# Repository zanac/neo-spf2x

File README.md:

# Neo Geo AES/MVS cartridge with microSD: format, packer, loader and gateware

🇬🇧 English · [🇮🇹 Italiano](README.it.md)

A Neo Geo cartridge (AES and MVS) that loads a game from a microSD card. The software side
(format, packer, loader) is written and tested; the FPGA gateware is simulated but not proven
on a console; the PCBs are not designed yet (the partition is in `docs/PCB.md`). See
`docs/ARCHITECTURE.md` for the status and the open points.

**Documentation is kept in English (`docs/`, this README) and in Italian (`docs/it/`,
`README.it.md`), and both versions are updated together** (`tests/check_docs.py`).

## Contents

| Path | What |
|------|------|
| `docs/FORMAT.md` | Specification of the `.ngpk` format and of the recipes |
| `docs/MVS.md`, `docs/PCB.md` | MVS/AES differences, MVS pinout and board partition (AES + MVS) |
| `docs/AES_PINOUT.md` | Signal names and pin numbers of the AES PROG and CHA connectors |
| `docs/TIMING.md` | Sprite, fix, bank switching and NEO-ZMC behaviour derived from Geolith, with what is missing |
| `docs/ARCHITECTURE.md` | Architecture, SDRAM map, contract with the FPGA, open points |
| `tools/ngpk.py` | Packer/inspector (Python 3, no dependencies) |
| `recipes/` | Recipes: Samurai Shodown III (example) and `spf2ng` (the project's game) |
| `docs/GATEWARE.md` | Status of the Verilog gateware and what the tests prove |
| `gateware/` | RTL and testbenches (Icarus Verilog): sprite (AES and MVS), fix, P bank, Z80 bank, SDRAM controller, arbiter, top |
| `docs/BOOT.md` | How the console sees the cartridge during loading (boot stub) |
| `boot/` | 68k source of the stub (`stub.S`) and binary |
| `docs/PROTECTIONS.md` | Protected games and special cartridges (from MAME): what each needs, 128 MiB, open risks |
| `docs/COMPONENTS.md` | I/O budget, choice of FPGA, SDRAM, MCU, translators and open hardware points |
| `hardware/` | `gen_signals.py`, `signals.csv` (162 AES signals), `signals_mvs.csv` (184 MVS pins), `mvs_pins.csv`, `extract_kicad_pins.py` |
| `firmware/` | `.ngpk` parser and loader in portable C99, plus PC tests |
| `tests/` | Packer tests, documentation check and the script that runs everything |

ROM files are not included: you need your own dumps.

**License:** GPL-3.0-or-later, text in `LICENSE`.

## Usage

```sh
# create a package (the recipe lists the files, --base-dir says where they are)
python3 tools/ngpk.py pack recipes/samsho3.json --base-dir /path/to/romset -o samsho3.ngpk

python3 tools/ngpk.py info   samsho3.ngpk    # regions, sizes, CRC
python3 tools/ngpk.py verify samsho3.ngpk    # re-check the CRCs
python3 tools/ngpk.py unpack samsho3.ngpk -o out/   # P.bin, C.bin, ...
# unpack --canonical brings C and S back to MAME order; pack uses the sdram1 layout (docs/FORMAT.md)

# tests (without ROMs it uses a synthetic game; with a folder it also uses the romset)
tests/run_all.sh
tests/run_all.sh /path/to/romset
```

Copy the `.ngpk` files onto the microSD: the loader reads them through the MCU's file system
(FatFS).

## Adding a game

Write a recipe (see `docs/FORMAT.md`): which files go in which region and with which
operation (`concat`, `swap16`, `interleave8`). The packer checks that `NEO-GEO` is at `0x100`
of the P, so a wrong swap does not go unnoticed. Games requiring protections or encryption
(SMA, PCM2, CMC, PVC...) are not supported yet and are rejected.

## Porting the loader to an MCU

`firmware/ngsd_loader.c` does not depend on the hardware. Four functions in `ngsd_hal_t` are
implemented: reading from the file on the SD (FatFS), writing into SDRAM through the FPGA,
writing the FPGA registers and, if needed, a progress bar. The code compiles with `-std=c99`
without libraries.

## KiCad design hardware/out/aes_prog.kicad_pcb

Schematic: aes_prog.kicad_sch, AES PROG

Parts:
C1, C2, C3, C4, C5, C6, C7, C8, C9, C10, C11, C12, C13, C14, C15, C16, C17, C18, C19, C20, C21, C22, C23, C24, C27, C28, C29, C30, C31, C32, C33, C34, C35, C36, C38, C42: 100n; C_0402_1005Metric
C25, C26: 22u; C_1206_3216Metric
C37, C39: 1u; C_0402_1005Metric
C40, C41: 15p; C_0402_1005Metric
D1: MCU; LED_0603_1608Metric
J1: AES PROG edge A; neogeo-aes-a-side-edge
J2: AES PROG edge B; neogeo-aes-b-side-edge
J3: LINK1; Hirose_DF12NB3.0-80DP-0.5V51_2x40_P0.50mm_Vertical
J4: LINK2; Hirose_DF12NB3.0-80DP-0.5V51_2x40_P0.50mm_Vertical
J5: microSD; microSD_HC_Hirose_DM3AT-SF-PEJM5
J6: USB/SWD pads; PinHeader_1x04_P1.27mm_Vertical
J7: SWD; PinHeader_1x03_P1.27mm_Vertical
R1, R2, R3, R4, R5, R6: 10k; R_0402_1005Metric
R7, R10, R11: 1k; R_0402_1005Metric
R8, R9: 27; R_0402_1005Metric
R12: 0; R_0402_1005Metric
SW1: RESET; SW_SPST_PTS810
SW2: BOOTSEL; SW_SPST_PTS810
U1, U2, U3, U4, U5, U6: SN74ALVC164245DGG; TSSOP-48_6.1x12.5mm_P0.5mm
U7: RP2040; QFN-56-1EP_7x7mm_P0.4mm_EP3.2x3.2mm
U8: W25Q128JVS; SOIC-8W_5.3x5.3mm_P1.27mm
Y1: 12MHz ABM8-272-T3; Crystal_SMD_3225-4Pin_3.2x2.5mm

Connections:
4MB: J4.29, U4.29 (2A6)
68KCLKB: J3.65, U3.30 (2A5)
+3V3: C1.1, C2.1, C5.1, C6.1, C9.1, C10.1, C13.1, C14.1, C17.1, C18.1, C21.1, C22.1, C26.1, C27.1, C28.1, C29.1, C30.1, C31.1, C32.1, C33.1, C34.1, C35.1, C36.1, C39.1, C42.1, J4.46, J4.47, J4.48, J5.4 (VDD), R1.2, R2.2, R3.2, R4.2, R5.2, R6.2, U1.31 (VCCA), U1.42 (VCCA), U2.31 (VCCA), U2.42 (VCCA), U3.31 (VCCA), U3.42 (VCCA), U4.31 (VCCA), U4.42 (VCCA), U5.1 (1DIR), U5.31 (VCCA), U5.42 (VCCA), U6.25 (2~OE), U6.31 (VCCA), U6.42 (VCCA), U7.1 (IOVDD), U7.10 (IOVDD), U7.22 (IOVDD), U7.33 (IOVDD), U7.42 (IOVDD), U7.43 (ADC_AVDD), U7.44 (VREG_IN), U7.48 (USB_VDD), U7.49 (IOVDD), U8.8 (VCC)
+5V: C3.1, C4.1, C7.1, C8.1, C11.1, C12.1, C15.1, C16.1, C19.1, C20.1, C23.1, C24.1, C25.1, J1.25, J1.26, J1.27, J2.25, J2.26, J2.27, J4.49, J4.50, J6.4, U1.7 (VCCB), U1.18 (VCCB), U2.7 (VCCB), U2.18 (VCCB), U3.7 (VCCB), U3.18 (VCCB), U4.7 (VCCB), U4.18 (VCCB), U5.7 (VCCB), U5.18 (VCCB), U6.7 (VCCB), U6.18 (VCCB)
A1: J3.2, U2.47 (1A1)
A2: J3.5, U2.46 (1A2)
A3: J3.7, U2.44 (1A3)
A4: J3.10, U2.43 (1A4)
A5: J3.13, U2.41 (1A5)
A6: J3.15, U2.40 (1A6)
A7: J3.18, U2.38 (1A7)
A8: J3.21, U2.37 (1A8)
A9: J3.23, U2.36 (2A1)
A10: J3.26, U2.35 (2A2)
A11: J3.29, U2.33 (2A3)
A12: J3.31, U2.32 (2A4)
A13: J3.34, U2.30 (2A5)
A14: J3.37, U2.29 (2A6)
A15: J3.39, U2.27 (2A7)
A16: J3.42, U2.26 (2A8)
A17: J3.45, U3.46 (1A2)
A18: J3.47, U3.43 (1A4)
A19: J3.50, U3.40 (1A6)
AS: J3.46, U3.44 (1A3)
BOOTSEL_N: R7.1, SW2.1
D0: J3.1, U1.47 (1A1)
D1: J3.3, U1.46 (1A2)
D2: J3.6, U1.44 (1A3)
D3: J3.9, U1.43 (1A4)
D4: J3.11, U1.41 (1A5)
D5: J3.14, U1.40 (1A6)
D6: J3.17, U1.38 (1A7)
D7: J3.19, U1.37 (1A8)
D8: J3.22, U1.36 (2A1)
D9: J3.25, U1.35 (2A2)
D10: J3.27, U1.33 (2A3)
D11: J3.30, U1.32 (2A4)
D12: J3.33, U1.30 (2A5)
D13: J3.35, U1.29 (2A6)
D14: J3.38, U1.27 (2A7)
D15: J3.41, U1.26 (2A8)
DIR_D: J4.42, U1.1 (1DIR), U1.24 (2DIR)
DIR_SDPAD: J4.43, U6.1 (1DIR)
DIR_SDRAD: J4.45, U5.24 (2DIR)
GND: C1.2, C2.2, C3.2, C4.2, C5.2, C6.2, C7.2, C8.2, C9.2, C10.2, C11.2, C12.2, C13.2, C14.2, C15.2, C16.2, C17.2, C18.2, C19.2, C20.2, C21.2, C22.2, C23.2, C24.2, C25.2, C26.2, C27.2, C28.2, C29.2, C30.2, C31.2, C32.2, C33.2, C34.2, C35.2, C36.2, C37.2, C38.2, C39.2, C40.2, C41.2, C42.2, J1.1, J1.2, J1.49, J1.50, J2.1, J2.2, J2.49, J2.50, J3.4, J3.8, J3.12, J3.16, J3.20, J3.24, J3.28, J3.32, J3.36, J3.40, J3.44, J3.48, J3.52, J3.56, J3.60, J3.64, J3.68, J3.72, J3.76, J3.80, J4.4, J4.8, J4.12, J4.16, J4.20, J4.24, J4.28, J4.32, J4.36, J4.40, J4.44, J4.51, J4.52, J4.53, J4.54, J4.55, J4.56, J4.57, J4.58, J4.59, J4.60, J4.61, J4.62, J4.63, J4.64, J4.65, J4.66, J4.67, J4.68, J4.69, J4.70, J4.71, J4.72, J4.73, J4.74, J4.75, J4.76, J4.77, J4.78, J4.79, J4.80, J5.6 (VSS), J5.10 (DET_A), J5.11 (SHIELD), J6.3, J7.2, R12.2, SW1.2, SW2.2, U1.4 (GND), U1.10 (GND), U1.15 (GND), U1.21 (GND), U1.28 (GND), U1.34 (GND), U1.39 (GND), U1.45 (GND), U2.1 (1DIR), U2.4 (GND), U2.10 (GND), U2.15 (GND), U2.21 (GND), U2.24 (2DIR), U2.28 (GND), U2.34 (GND), U2.39 (GND), U2.45 (GND), U3.1 (1DIR), U3.4 (GND), U3.10 (GND), U3.15 (GND), U3.21 (GND), U3.24 (2DIR), U3.28 (GND), U3.34 (GND), U3.39 (GND), U3.45 (GND), U4.1 (1DIR), U4.4 (GND), U4.10 (GND), U4.15 (GND), U4.21 (GND), U4.22 (2B7), U4.23 (2B8), U4.24 (2DIR), U4.26 (2A8), U4.27 (2A7), U4.28 (GND), U4.34 (GND), U4.39 (GND), U4.45 (GND), U5.4 (GND), U5.8 (1B5), U5.9 (1B6), U5.10 (GND), U5.11 (1B7), U5.12 (1B8), U5.15 (GND), U5.21 (GND), U5.28 (GND), U5.34 (GND), U5.37 (1A8), U5.38 (1A7), U5.39 (GND), U5.40 (1A6), U5.41 (1A5), U5.45 (GND), U6.4 (GND), U6.10 (GND), U6.13 (2B1), U6.14 (2B2), U6.15 (GND), U6.16 (2B3), U6.17 (2B4), U6.19 (2B5), U6.20 (2B6), U6.21 (GND), U6.22 (2B7), U6.23 (2B8), U6.24 (2DIR), U6.26 (2A8), U6.27 (2A7), U6.28 (GND), U6.29 (2A6), U6.30 (2A5), U6.32 (2A4), U6.33 (2A3), U6.34 (GND), U6.35 (2A2), U6.36 (2A1), U6.39 (GND), U6.45 (GND), U7.19 (TESTEN), U7.57 (GND), U8.4 (GND), Y1.2, Y1.4
LED_A: D1.2 (A), R11.1
LED_K: D1.1 (K), R12.1
LED_MCU: R11.2, U7.37 (GPIO25)
MCU_INT: J4.41, U7.17 (GPIO14)
MCU_RUN: J4.39, U7.16 (GPIO13)
OE_PRG_N: J4.38, U1.25 (2~OE), U1.48 (1~OE), U2.25 (2~OE), U2.48 (1~OE), U3.25 (2~OE), U3.48 (1~OE), U4.25 (2~OE), U4.48 (1~OE), U5.25 (2~OE), U5.48 (1~OE), U6.48 (1~OE)
PDTACK: J3.63, U5.43 (1A4)
PORTADRS: J4.27, U4.30 (2A5)
PORTOEL: J3.57, U3.35 (2A2)
PORTOEU: J3.54, U3.36 (2A1)
PORTWEL: J3.62, U3.32 (2A4)
PORTWEU: J3.59, U3.33 (2A3)
PWAIT0: J3.61, U5.44 (1A3)
PWAIT1: J3.58, U5.46 (1A2)
QSPI_SCLK: U7.52 (QSPI_SCLK), U8.6 (CLK)
QSPI_SD0: U7.53 (QSPI_SD0), U8.5 (DI(IO0))
QSPI_SD1: U7.55 (QSPI_SD1), U8.2 (DO(IO1))
QSPI_SD2: U7.54 (QSPI_SD2), U8.3 (IO2)
QSPI_SD3: U7.51 (QSPI_SD3), U8.7 (IO3)
QSPI_SS: R7.2, U7.56 (QSPI_SS), U8.1 (~CS)
RESET: J3.67, U3.29 (2A6)
ROMOE: J3.53, U3.37 (1A8)
ROMOEL: J3.51, U3.38 (1A7)
ROMOEU: J3.49, U3.41 (1A5)
ROMWAIT: J3.55, U5.47 (1A1)
RP_DVDD: C37.1, C38.1, U7.23 (DVDD), U7.45 (VREG_VOUT), U7.50 (DVDD)
RP_RUN: R6.1, SW1.1, U7.26 (RUN)
R_W: J3.43, U3.47 (1A1)
SDPA8: J4.11, U4.47 (1A1)
SDPA9: J4.14, U4.44 (1A3)
SDPA10: J4.17, U4.41 (1A5)
SDPA11: J4.19, U4.38 (1A7)
SDPAD0: J3.70, U6.47 (1A1)
SDPAD1: J3.73, U6.46 (1A2)
SDPAD2: J3.75, U6.44 (1A3)
SDPAD3: J3.78, U6.43 (1A4)
SDPAD4: J4.1, U6.41 (1A5)
SDPAD5: J4.3, U6.40 (1A6)
SDPAD6: J4.6, U6.38 (1A7)
SDPAD7: J4.9, U6.37 (1A8)
SDPMPX: J4.22, U4.36 (2A1)
SDPOE: J4.25, U4.33 (2A3)
SDRA8: J4.7, U3.27 (2A7)
SDRA9: J4.10, U3.26 (2A8)
SDRA20: J4.13, U4.46 (1A2)
SDRA21: J4.15, U4.43 (1A4)
SDRA22: J4.18, U4.40 (1A6)
SDRA23: J4.21, U4.37 (1A8)
SDRAD0: J3.66, U5.36 (2A1)
SDRAD1: J3.69, U5.35 (2A2)
SDRAD2: J3.71, U5.33 (2A3)
SDRAD3: J3.74, U5.32 (2A4)
SDRAD4: J3.77, U5.30 (2A5)
SDRAD5: J3.79, U5.29 (2A6)
SDRAD6: J4.2, U5.27 (2A7)
SDRAD7: J4.5, U5.26 (2A8)
SDRMPX: J4.23, U4.35 (2A2)
SDROE: J4.26, U4.32 (2A4)
SD_CLK: J5.5 (CLK), U7.8 (GPIO6)
SD_CMD: J5.3 (CMD), R5.1, U7.9 (GPIO7)
SD_D0: J5.7 (DAT0), R1.1, U7.11 (GPIO8)
SD_D1: J5.8 (DAT1), R2.1, U7.12 (GPIO9)
SD_D2: J5.1 (DAT2), R3.1, U7.13 (GPIO10)
SD_D3: J5.2 (DAT3/CD), R4.1, U7.14 (GPIO11)
SD_DET: J5.9 (DET_B), U7.15 (GPIO12)
SPI_CS_N: J4.31, U7.3 (GPIO1)
SPI_IO0: J4.33, U7.4 (GPIO2)
SPI_IO1: J4.34, U7.5 (GPIO3)
SPI_IO2: J4.35, U7.6 (GPIO4)
SPI_IO3: J4.37, U7.7 (GPIO5)
SPI_SCLK: J4.30, U7.2 (GPIO0)
SWCLK: J7.1, U7.24 (SWCLK)
SWD: J7.3, U7.25 (SWD)
USB_DM: J6.1, R8.2
USB_DM_R: R8.1, U7.46 (USB_DM)
USB_DP: J6.2, R9.2
USB_DP_R: R9.1, U7.47 (USB_DP)
XIN: C40.1, U7.20 (XIN), Y1.1
XOUT: R10.1, U7.21 (XOUT)
XOUT_R: C41.1, R10.2, Y1.3
X_4MB: J2.48, U4.20 (2B6)
X_68KCLKB: J1.32, U3.19 (2B5)
X_A1: J2.3, U2.2 (1B1)
X_A2: J2.4, U2.3 (1B2)
X_A3: J2.5, U2.5 (1B3)
X_A4: J2.6, U2.6 (1B4)
X_A5: J2.7, U2.8 (1B5)
X_A6: J2.8, U2.9 (1B6)
X_A7: J2.9, U2.11 (1B7)
X_A8: J2.10, U2.12 (1B8)
X_A9: J2.11, U2.13 (2B1)
X_A10: J2.12, U2.14 (2B2)
X_A11: J2.13, U2.16 (2B3)
X_A12: J2.14, U2.17 (2B4)
X_A13: J2.15, U2.19 (2B5)
X_A14: J2.16, U2.20 (2B6)
X_A15: J2.17, U2.22 (2B7)
X_A16: J2.18, U2.23 (2B8)
X_A17: J2.19, U3.3 (1B2)
X_A18: J2.20, U3.6 (1B4)
X_A19: J2.21, U3.9 (1B6)
X_AS: J1.20, U3.5 (1B3)
X_D0: J1.3, U1.2 (1B1)
X_D1: J1.4, U1.3 (1B2)
X_D2: J1.5, U1.5 (1B3)
X_D3: J1.6, U1.6 (1B4)
X_D4: J1.7, U1.8 (1B5)
X_D5: J1.8, U1.9 (1B6)
X_D6: J1.9, U1.11 (1B7)
X_D7: J1.10, U1.12 (1B8)
X_D8: J1.11, U1.13 (2B1)
X_D9: J1.12, U1.14 (2B2)
X_D10: J1.13, U1.16 (2B3)
X_D11: J1.14, U1.17 (2B4)
X_D12: J1.15, U1.19 (2B5)
X_D13: J1.16, U1.20 (2B6)
X_D14: J1.17, U1.22 (2B7)
X_D15: J1.18, U1.23 (2B8)
X_PDTACK: J2.31, U5.6 (1B4)
X_PORTADRS: J1.48, U4.19 (2B5)
X_PORTOEL: J1.29, U3.14 (2B2)
X_PORTOEU: J1.28, U3.13 (2B1)
X_PORTWEL: J1.31, U3.17 (2B4)
X_PORTWEU: J1.30, U3.16 (2B3)
X_PWAIT0: J2.30, U5.5 (1B3)
X_PWAIT1: J2.29, U5.3 (1B2)
X_RESET: J1.33, U3.20 (2B6)
X_ROMOE: J2.22, U3.12 (1B8)
X_ROMOEL: J1.22, U3.11 (1B7)
X_ROMOEU: J1.21, U3.8 (1B5)
X_ROMWAIT: J2.28, U5.2 (1B1)
X_R_W: J1.19, U3.2 (1B1)
X_SDPA8: J1.42, U4.2 (1B1)
X_SDPA9: J1.43, U4.5 (1B3)
X_SDPA10: J1.44, U4.8 (1B5)
X_SDPA11: J1.45, U4.11 (1B7)
X_SDPAD0: J1.34, U6.2 (1B1)
X_SDPAD1: J1.35, U6.3 (1B2)
X_SDPAD2: J1.36, U6.5 (1B3)
X_SDPAD3: J1.37, U6.6 (1B4)
X_SDPAD4: J1.38, U6.8 (1B5)
X_SDPAD5: J1.39, U6.9 (1B6)
X_SDPAD6: J1.40, U6.11 (1B7)
X_SDPAD7: J1.41, U6.12 (1B8)
X_SDPMPX: J1.46, U4.13 (2B1)
X_SDPOE: J1.47, U4.16 (2B3)
X_SDRA8: J2.40, U3.22 (2B7)
X_SDRA9: J2.41, U3.23 (2B8)
X_SDRA20: J2.42, U4.3 (1B2)
X_SDRA21: J2.43, U4.6 (1B4)
X_SDRA22: J2.44, U4.9 (1B6)
X_SDRA23: J2.45, U4.12 (1B8)
X_SDRAD0: J2.32, U5.13 (2B1)
X_SDRAD1: J2.33, U5.14 (2B2)
X_SDRAD2: J2.34, U5.16 (2B3)
X_SDRAD3: J2.35, U5.17 (2B4)
X_SDRAD4: J2.36, U5.19 (2B5)
X_SDRAD5: J2.37, U5.20 (2B6)
X_SDRAD6: J2.38, U5.22 (2B7)
X_SDRAD7: J2.39, U5.23 (2B8)
X_SDRMPX: J2.46, U4.14 (2B2)
X_SDROE: J2.47, U4.17 (2B4)

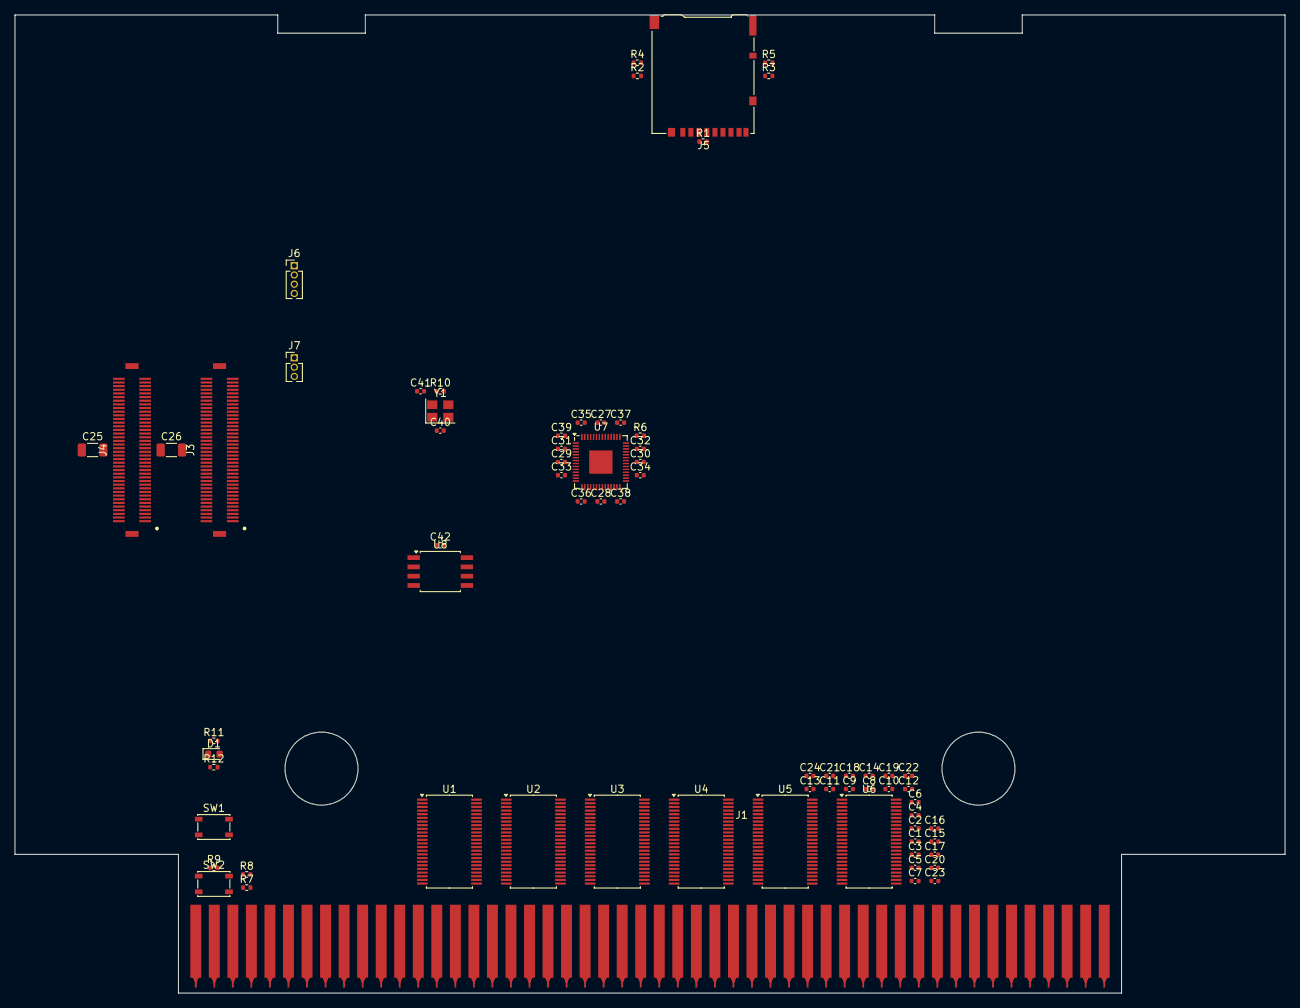
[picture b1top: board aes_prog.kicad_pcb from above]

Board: 6 copper layers, 174.0 x 134.0 mm, 73 parts (1 on the bottom side), 207 nets, no tracks yet.

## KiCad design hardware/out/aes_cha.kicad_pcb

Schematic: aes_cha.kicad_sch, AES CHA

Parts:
C1, C2, C3, C4, C5, C6, C7, C8, C9, C10, C11, C12, C13, C14, C15, C16, C17, C18, C19, C20, C21, C22, C23, C24, C28, C29, C30, C31, C32, C33, C34, C35, C36, C38, C39, C40, C41, C42, C43, C44, C45, C46, C47, C48, C49, C50, C51, C52, C53, C54, C55, C56, C57, C58, C59, C67, C68, C69, C70, C71, C72, C73, C74, C75, C77, C78, C79, C80, C81, C82, C83, C84, C94, C95, C96, C97, C98, C99, C100, C101, C102, C103, C104, C105, C106, C107, C108, C109, C110, C111, C112, C113, C114, C115, C116, C117: 100n; C_0402_1005Metric
C25, C26, C27, C37, C60, C61, C62, C63, C64, C65, C66: 10u; C_0603_1608Metric
C76, C85, C86, C93: 10u; C_0805_2012Metric
C87, C88, C89, C90, C91, C92: 22u; C_1206_3216Metric
D1: DONE; LED_0603_1608Metric
FB1: 120R@100MHz; L_0603_1608Metric
J1: JTAG; PinHeader_2x05_P1.27mm_Vertical_SMD
J2: AES CHA edge A; neogeo-aes-a-side-edge
J3: AES CHA edge B; neogeo-aes-b-side-edge
J4: LINK1; Hirose_DF12NB3.0-80DS-0.5V51_2x40_P0.50mm_Vertical
J5: LINK2; Hirose_DF12NB3.0-80DS-0.5V51_2x40_P0.50mm_Vertical
L1, L2, L3: 2.2uH NRS4018T2R2MDGJV; L_Taiyo-Yuden_NR-40xx
R1, R2, R3, R6, R7, R8, R9, R10, R11, R12, R19: 4.7k; R_0402_1005Metric
R4, R5, R25: 0; R_0402_1005Metric
R13, R24: 1k; R_0402_1005Metric
R14: 33; R_0402_1005Metric
R15, R16, R17, R18, R20, R21, R22, R23, R26, R27, R28, R29, R30, R31, R32, R33, R36: 10k; R_0402_1005Metric
R34: 453k; R_0402_1005Metric
R35, R39: 100k; R_0402_1005Metric
R37: 12k; R_0402_1005Metric
R38: 316k; R_0402_1005Metric
SW1: PROGRAMN; SW_SPST_PTS810
U1: LFE5U-45F-8BG554; BGA-554_26x26_23.0x23.0mm_P0.8mm
U2: W25Q128JVS; SOIC-8W_5.3x5.3mm_P1.27mm
U3, U4: AS4C32M16SB / IS42S16320D (512Mbit x16); TSOP-II-54_22.2x10.16mm_P0.8mm
U5, U6, U7: TLV62569; SOT-23-5
U8, U9, U10, U11, U12, U13: SN74ALVC164245DGG; TSSOP-48_6.1x12.5mm_P0.5mm

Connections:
2H1: U1.D5 (PT9A), U8.43 (1A4)
4MB: J5.29, U1.P5 (PL47B)
8M: U1.E11 (PT36A/PCLKT0_1), U11.40 (1A6)
12M: U1.D11 (PT36B/PCLKC0_1), U8.44 (1A3)
24M: U1.A2 (PT4A/ULC_GPLL1T_IN), U11.41 (1A5)
68KCLKB: J4.65, U1.B11 (PT33B/GR_PCLK0_0)
+1V1: C1.1, C2.1, C3.1, C4.1, C5.1, C6.1, C7.1, C8.1, C9.1, C10.1, C11.1, C12.1, C13.1, C14.1, C15.1, C16.1, C17.1, C18.1, C19.1, C20.1, C21.1, C22.1, C23.1, C24.1, C25.1, C26.1, C27.1, C89.1, C90.1, L2.2, R36.1, U1.K11 (VCC), U1.K12 (VCC), U1.K13 (VCC), U1.K14 (VCC), U1.K15 (VCC), U1.K16 (VCC), U1.L10 (VCC), U1.L17 (VCC), U1.M10 (VCC), U1.M17 (VCC), U1.N10 (VCC), U1.N17 (VCC), U1.P10 (VCC), U1.P17 (VCC), U1.R10 (VCC), U1.R17 (VCC), U1.T10 (VCC), U1.T11 (VCC), U1.T12 (VCC), U1.T13 (VCC), U1.T14 (VCC), U1.T15 (VCC), U1.T16 (VCC), U1.T17 (VCC)
+2V5: C91.1, C92.1, FB1.1, L3.2, R38.1
+3V3: C38.1, C39.1, C40.1, C41.1, C42.1, C43.1, C44.1, C45.1, C46.1, C47.1, C48.1, C49.1, C50.1, C51.1, C52.1, C53.1, C54.1, C55.1, C56.1, C57.1, C58.1, C59.1, C60.1, C61.1, C62.1, C63.1, C64.1, C65.1, C66.1, C67.1, C68.1, C69.1, C70.1, C71.1, C72.1, C73.1, C74.1, C75.1, C76.1, C77.1, C78.1, C79.1, C80.1, C81.1, C82.1, C83.1, C84.1, C85.1, C87.1, C88.1, C93.1, C94.1, C95.1, C98.1, C99.1, C102.1, C103.1, C106.1, C107.1, C110.1, C111.1, C114.1, C115.1, J1.1, J5.46, J5.47, J5.48, L1.2, R1.2, R2.2, R3.2, R6.2, R7.2, R8.2, R9.2, R10.2, R11.2, R13.2, R15.2, R16.2, R17.2, R18.2, R19.2, R20.2, R21.2, R23.2, R27.2, R28.2, R30.2, R31.2, R32.2, R33.2, R34.1, U1.H10 (VCCIO0), U1.H12 (VCCIO0), U1.H13 (VCCIO0), U1.H15 (VCCIO1), U1.H16 (VCCIO1), U1.H18 (VCCIO1), U1.J19 (VCCIO2), U1.K8 (VCCIO7), U1.L19 (VCCIO2), U1.M8 (VCCIO7), U1.M19 (VCCIO2), U1.N8 (VCCIO7), U1.N19 (VCCIO2), U1.P8 (VCCIO6), U1.P19 (VCCIO3), U1.R8 (VCCIO6), U1.R19 (VCCIO3), U1.U8 (VCCIO6), U1.U19 (VCCIO3), U1.V8 (VCCIO6), U1.V10 (VCCIO8), U1.V11 (VCCIO8), U2.8 (VCC), U3.1 (VDD), U3.3 (VDDQ), U3.9 (VDDQ), U3.14 (VDD), U3.27 (VDD), U3.43 (VDDQ), U3.49 (VDDQ), U4.1 (VDD), U4.3 (VDDQ), U4.9 (VDDQ), U4.14 (VDD), U4.27 (VDD), U4.43 (VDDQ), U4.49 (VDDQ), U6.1 (EN), U6.4 (VIN), U7.1 (EN), U7.4 (VIN), U8.31 (VCCA), U8.42 (VCCA), U9.31 (VCCA), U9.42 (VCCA), U10.31 (VCCA), U10.42 (VCCA), U11.24 (2DIR), U11.31 (VCCA), U11.42 (VCCA), U12.1 (1DIR), U12.24 (2DIR), U12.31 (VCCA), U12.42 (VCCA), U13.25 (2~OE), U13.31 (VCCA), U13.42 (VCCA)
+5V: C86.1, C96.1, C97.1, C100.1, C101.1, C104.1, C105.1, C108.1, C109.1, C112.1, C113.1, C116.1, C117.1, J2.25, J2.26, J2.27, J3.25, J3.26, J3.27, J5.49, J5.50, U5.1 (EN), U5.4 (VIN), U8.7 (VCCB), U8.18 (VCCB), U9.7 (VCCB), U9.18 (VCCB), U10.7 (VCCB), U10.18 (VCCB), U11.7 (VCCB), U11.18 (VCCB), U12.7 (VCCB), U12.18 (VCCB), U13.7 (VCCB), U13.18 (VCCB)
A1: J4.2, U1.E24 (PR17C)
A2: J4.5, U1.F22 (PR23A)
A3: J4.7, U1.F26 (PR20B)
A4: J4.10, U1.H26 (PR35D/PCLKC3_0)
A5: J4.13, U1.H24 (PR35A/PCLKT3_1)
A6: J4.15, U1.H21 (PR23D)
A7: J4.18, U1.J26 (PR38B)
A8: J4.21, U1.J23 (PR29B)
A9: J4.23, U1.K26 (PR41C)
A10: J4.26, U1.K25 (PR38A/GR_PCLK3_0)
A11: J4.29, U1.K22 (PR29A/GR_PCLK2_1)
A12: J4.31, U1.L26 (PR41D)
A13: J4.34, U1.L24 (PR38D)
A14: J4.37, U1.L22 (PR26D)
A15: J4.39, U1.M26 (PR41B)
A16: J4.42, U1.M21 (PR29C/GR_PCLK2_0)
A17: J4.45, U1.N25 (PR44B/VREF1_3)
A18: J4.47, U1.N26 (PR44A)
A19: J4.50, U1.N21 (PR32C/PCLKT2_0)
AS: J4.46, U1.N24 (PR44C)
BUCK25_FB: R38.2, R39.1, U7.5 (FB)
BUCK25_SW: L3.1, U7.3 (SW)
BUCK33_FB: R34.2, R35.1, U5.5 (FB)
BUCK33_SW: L1.1, U5.3 (SW)
BUCK_FB: R36.2, R37.1, U6.5 (FB)
BUCK_SW: L2.1, U6.3 (SW)
CA4: U1.C8 (PT20B), U8.37 (1A8)
CFG0: R1.1, R4.1, U1.AF4 (CFG_0)
CFG1: R2.1, U1.AE4 (CFG_1)
CFG2: R3.1, R5.1, U1.AD4 (CFG_2)
D0: J4.1, U1.E26 (PR17B)
D1: J4.3, U1.F23 (PR23B)
D2: J4.6, U1.F24 (PR20D)
D3: J4.9, U1.F25 (PR20A)
D4: J4.11, U1.H25 (PR35C/PCLKT3_0)
D5: J4.14, U1.H23 (PR26C)
D6: J4.17, U1.H22 (PR23C/VREF1_2)
D7: J4.19, U1.J24 (PR35B/PCLKC3_1)
D8: J4.22, U1.J21 (PR26A)
D9: J4.25, U1.K24 (PR38C/GR_PCLK3_1)
D10: J4.27, U1.K23 (PR32A/PCLKT2_1)
D11: J4.30, U1.K21 (PR26B)
D12: J4.33, U1.L25 (PR41A)
D13: J4.35, U1.L23 (PR32B/PCLKC2_1)
D14: J4.38, U1.M24 (PR44D)
D15: J4.41, U1.M23 (PR29D)
DIR_D: J5.42, U1.P3 (PL59D)
DIR_SDD: R22.1, U1.E23 (PR20C), U13.1 (1DIR)
DIR_SDPAD: J5.43, U1.P2 (PL62A)
DIR_SDRAD: J5.45, U1.P1 (PL62B)
DOTA: U1.D16 (PT53A), U12.47 (1A1)
DOTB: U1.C17 (PT60B), U12.46 (1A2)
EVEN: U1.B6 (PT13B), U8.41 (1A5)
FIXD0: U1.A4 (PT6B), U11.36 (2A1)
FIXD1: U1.A5 (PT15A), U11.35 (2A2)
FIXD2: U1.C5 (PT9B), U11.33 (2A3)
FIXD3: U1.A6 (PT15B), U11.32 (2A4)
FIXD4: U1.C6 (PT13A), U11.30 (2A5)
FIXD5: U1.E6 (PT11A), U11.29 (2A6)
FIXD6: U1.E8 (PT22A), U11.27 (2A7)
FIXD7: U1.B8 (PT20A), U11.26 (2A8)
FLASH_CLK: R13.1, R14.2, U2.6 (CLK)
FLASH_CLK_F: R14.1, U1.AE3 (CCLK/MCLK/SCK)
FLASH_CS_N: R19.1, U1.AA2 (PB15A/HOLDN/DI/BUSY/CSSPIN/CEN), U2.1 (~CS)
FLASH_DI: R15.1, U1.AE2 (PB11B/D0/MOSI/IO0), U2.5 (DI(IO0))
FLASH_DO: R16.1, U1.AD2 (PB11A/D1/MISO/IO1), U2.2 (DO(IO1))
FLASH_IO2: R17.1, U1.AF2 (PB9B/D2/IO2), U2.3 (IO2)
FLASH_IO3: R18.1, U1.AE1 (PB9A/D3/IO3), U2.7 (IO3)
FPGA_DONE: R8.1, R24.2, U1.AC4 (DONE)
FPGA_INITN: R6.1, U1.AF3 (INITN)
FPGA_PROGRAMN: R7.1, SW1.1, U1.AB4 (PROGRAMN)
GAD0: U1.B17 (PT60A), U12.44 (1A3)
GAD1: U1.A18 (PT71A), U12.43 (1A4)
GAD2: U1.C18 (PT65A), U12.41 (1A5)
GAD3: U1.B19 (PT69B), U12.40 (1A6)
GBD0: U1.D19 (PT67B), U12.38 (1A7)
GBD1: U1.E21 (PT78B), U12.37 (1A8)
GBD2: U1.C21 (PT76B), U12.36 (2A1)
GBD3: U1.A21 (PT74A), U12.35 (2A2)
GND: C1.2, C2.2, C3.2, C4.2, C5.2, C6.2, C7.2, C8.2, C9.2, C10.2, C11.2, C12.2, C13.2, C14.2, C15.2, C16.2, C17.2, C18.2, C19.2, C20.2, C21.2, C22.2, C23.2, C24.2, C25.2, C26.2, C27.2, C28.2, C29.2, C30.2, C31.2, C32.2, C33.2, C34.2, C35.2, C36.2, C37.2, C38.2, C39.2, C40.2, C41.2, C42.2, C43.2, C44.2, C45.2, C46.2, C47.2, C48.2, C49.2, C50.2, C51.2, C52.2, C53.2, C54.2, C55.2, C56.2, C57.2, C58.2, C59.2, C60.2, C61.2, C62.2, C63.2, C64.2, C65.2, C66.2, C67.2, C68.2, C69.2, C70.2, C71.2, C72.2, C73.2, C74.2, C75.2, C76.2, C77.2, C78.2, C79.2, C80.2, C81.2, C82.2, C83.2, C84.2, C85.2, C86.2, C87.2, C88.2, C89.2, C90.2, C91.2, C92.2, C93.2, C94.2, C95.2, C96.2, C97.2, C98.2, C99.2, C100.2, C101.2, C102.2, C103.2, C104.2, C105.2, C106.2, C107.2, C108.2, C109.2, C110.2, C111.2, C112.2, C113.2, C114.2, C115.2, C116.2, C117.2, J1.3, J1.5, J1.9, J2.1, J2.2, J2.49, J2.50, J3.1, J3.2, J3.49, J3.50, J4.4, J4.8, J4.12, J4.16, J4.20, J4.24, J4.28, J4.32, J4.36, J4.40, J4.44, J4.48, J4.52, J4.56, J4.60, J4.64, J4.68, J4.72, J4.76, J4.80, J5.4, J5.8, J5.12, J5.16, J5.20, J5.24, J5.28, J5.32, J5.36, J5.40, J5.44, J5.51, J5.52, J5.53, J5.54, J5.55, J5.56, J5.57, J5.58, J5.59, J5.60, J5.61, J5.62, J5.63, J5.64, J5.65, J5.66, J5.67, J5.68, J5.69, J5.70, J5.71, J5.72, J5.73, J5.74, J5.75, J5.76, J5.77, J5.78, J5.79, J5.80, R4.2, R5.2, R12.2, R22.2, R25.2, R26.2, R29.2, R35.2, R37.2, R39.2, SW1.2, U1.AA7 (GND), U1.AA9 (GND), U1.AA10 (GND), U1.AA12 (GND), U1.AA13 (GND), U1.AA14 (GND), U1.AA15 (GND), U1.AA17 (GND), U1.AA18 (GND), U1.AA20 (GND), U1.AB6 (GND), U1.AB7 (GND), U1.AB9 (GND), U1.AB10 (GND), U1.AB12 (GND), U1.AB13 (GND), U1.AB14 (GND), U1.AB15 (GND), U1.AB17 (GND), U1.AB18 (GND), U1.AB20 (GND), U1.AB21 (GND), U1.AB22 (GND), U1.AB23 (GND), U1.AC3 (GND), U1.AC6 (GND), U1.AC7 (GND), U1.AC8 (GND), U1.AC9 (GND), U1.AC10 (GND), U1.AC11 (GND), U1.AC12 (GND), U1.AC13 (GND), U1.AC14 (GND), U1.AC15 (GND), U1.AC16 (GND), U1.AC17 (GND), U1.AC18 (GND), U1.AC19 (GND), U1.AC20 (GND), U1.AC21 (GND), U1.AC22 (GND), U1.AC23 (GND), U1.AC24 (GND), U1.AC25 (GND), U1.AD6 (GND), U1.AD9 (GND), U1.AD12 (GND), U1.AD15 (GND), U1.AD18 (GND), U1.AD21 (GND), U1.AD24 (GND), U1.AE6 (GND), U1.AE7 (GND), U1.AE9 (GND), U1.AE10 (GND), U1.AE12 (GND), U1.AE13 (GND), U1.AE15 (GND), U1.AE16 (GND), U1.AE18 (GND), U1.AE19 (GND), U1.AE21 (GND), U1.AE22 (GND), U1.AE24 (GND), U1.AF5 (GND), U1.AF6 (GND), U1.AF7 (GND), U1.AF9 (GND), U1.AF10 (GND), U1.AF12 (GND), U1.AF13 (GND), U1.AF15 (GND), U1.AF16 (GND), U1.AF18 (GND), U1.AF19 (GND), U1.AF21 (GND), U1.AF22 (GND), U1.AF24 (GND), U1.B2 (GND), U1.B5 (GND), U1.B9 (GND), U1.B12 (GND), U1.B15 (GND), U1.B18 (GND), U1.B22 (GND), U1.B25 (GND), U1.E2 (GND), U1.E5 (GND), U1.E9 (GND), U1.E12 (GND), U1.E15 (GND), U1.E18 (GND), U1.E22 (GND), U1.E25 (GND), U1.H8 (GND), U1.H9 (GND), U1.H19 (GND), U1.J2 (GND), U1.J5 (GND), U1.J8 (GND), U1.J9 (GND), U1.J10 (GND), U1.J11 (GND), U1.J12 (GND), U1.J13 (GND), U1.J14 (GND), U1.J15 (GND), U1.J16 (GND), U1.J17 (GND), U1.J18 (GND), U1.J22 (GND), U1.J25 (GND), U1.K9 (GND), U1.K10 (GND), U1.K17 (GND), U1.K18 (GND), U1.L9 (GND), U1.L11 (GND), U1.L12 (GND), U1.L13 (GND), U1.L14 (GND), U1.L15 (GND), U1.L16 (GND), U1.L18 (GND), U1.M2 (GND), U1.M5 (GND), U1.M9 (GND), U1.M11 (GND), U1.M12 (GND), U1.M13 (GND), U1.M14 (GND), U1.M15 (GND), U1.M16 (GND), U1.M18 (GND), U1.M22 (GND), U1.M25 (GND), U1.N9 (GND), U1.N11 (GND), U1.N12 (GND), U1.N13 (GND), U1.N14 (GND), U1.N15 (GND), U1.N16 (GND), U1.N18 (GND), U1.P9 (GND), U1.P11 (GND), U1.P12 (GND), U1.P13 (GND), U1.P14 (GND), U1.P15 (GND), U1.P16 (GND), U1.P18 (GND), U1.R2 (GND), U1.R5 (GND), U1.R9 (GND), U1.R11 (GND), U1.R12 (GND), U1.R13 (GND), U1.R14 (GND), U1.R15 (GND), U1.R16 (GND), U1.R18 (GND), U1.R22 (GND), U1.R25 (GND), U1.T9 (GND), U1.T18 (GND), U1.U9 (GND), U1.U10 (GND), U1.U11 (GND), U1.U12 (GND), U1.U13 (GND), U1.U14 (GND), U1.U15 (GND), U1.U16 (GND), U1.U17 (GND), U1.U18 (GND), U1.V2 (GND), U1.V5 (GND), U1.V9 (GND), U1.V12 (GND), U1.V13 (GND), U1.V14 (GND), U1.V15 (GND), U1.V16 (GND), U1.V17 (GND), U1.V22 (GND), U1.V25 (GND), U1.W9 (GND), U1.W10 (GND), U1.W11 (GND)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
H: U1.D6 (PT11B), U8.40 (1A6)
JTAG_TCK: J1.4, R12.1, U1.AD5 (TCK)
JTAG_TDI: J1.8, R9.1, U1.AC5 (TDI)
JTAG_TDO: J1.6, R11.1, U1.AB5 (TDO)
JTAG_TMS: J1.2, R10.1, U1.AE5 (TMS)
LED_A: D1.2 (A), R24.1
LED_K: D1.1 (K), R25.1
LOAD: U1.D8 (PT22B), U8.38 (1A7)
MCU_INT: J5.41, U1.N2 (PL44B/VREF1_6)
MCU_RUN: J5.39, U1.N3 (PL44C)
OE_CHA_N: R20.1, U1.D23 (PR14A), U8.25 (2~OE), U8.48 (1~OE), U9.25 (2~OE), U9.48 (1~OE), U10.25 (2~OE), U10.48 (1~OE), U11.25 (2~OE), U11.48 (1~OE), U12.25 (2~OE), U12.48 (1~OE), U13.48 (1~OE)
OE_PRG_N: J5.38, R21.1, U1.R4 (PL50A)
P0: U1.A8 (PT18A), U8.36 (2A1)
P1: U1.C9 (PT24B), U8.35 (2A2)
P2: U1.D9 (PT24A), U8.33 (2A3)
P3: U1.A9 (PT18B), U8.32 (2A4)
P4: U1.A10 (PT31A), U8.30 (2A5)
P5: U1.B10 (PT29B), U8.29 (2A6)
P6: U1.D10 (PT27B), U8.27 (2A7)
P7: U1.C10 (PT29A), U8.26 (2A8)
P8: U1.E10 (PT27A), U9.47 (1A1)
P9: U1.A11 (PT31B), U9.46 (1A2)
P10: U1.C11 (PT33A/GR_PCLK0_1), U9.44 (1A3)
P11: U1.A12 (PT38A/PCLKT0_0), U9.43 (1A4)
P12: U1.B13 (PT49A), U9.41 (1A5)
P13: U1.C13 (PT47A/GR_PCLK1_0), U9.40 (1A6)
P14: U1.D13 (PT44A/PCLKT1_0), U9.38 (1A7)
P15: U1.E13 (PT42A/PCLKT1_1), U9.37 (1A8)
P16: U1.A13 (PT38B/PCLKC0_0), U9.36 (2A1)
P17: U1.A14 (PT51A), U9.35 (2A2)
P18: U1.B14 (PT49B), U9.33 (2A3)
P19: U1.C14 (PT47B/GR_PCLK1_1), U9.32 (2A4)
P20: U1.D14 (PT44B/PCLKC1_0), U9.30 (2A5)
P21: U1.E14 (PT42B/PCLKC1_1), U9.29 (2A6)
P22: U1.A15 (PT51B), U9.27 (2A7)
P23: U1.C16 (PT56B), U9.26 (2A8)
PCK1B: U1.A3 (PT4B/ULC_GPLL1C_IN), U8.47 (1A1)
PCK2B: U1.B4 (PT6A), U8.46 (1A2)
PDTACK: J4.63, U1.R23 (PR50A)
PORTADRS: J5.27, U1.P6 (PL47C)
PORTOEL: J4.57, U1.P21 (PR47C)
PORTOEU: J4.54, U1.P24 (PR59D)
PORTWEL: J4.62, U1.R21 (PR50C)
PORTWEU: J4.59, U1.R26 (PR62D)
PWAIT0: J4.61, U1.R24 (PR59C)
PWAIT1: J4.58, U1.P23 (PR47A)
RESET: J4.67, U1.T25 (PR62C)
ROMOE: J4.53, U1.P25 (PR62A)
ROMOEL: J4.51, U1.P26 (PR62B)
ROMOEU: J4.49, U1.N22 (PR32D/PCLKC2_0)
ROMWAIT: J4.55, U1.P22 (PR47B)
R_W: J4.43, U1.N23 (PR47D)
SDA0: U1.E16 (PT53B), U10.44 (1A3)
SDA1: U1.E17 (PT62B), U10.43 (1A4)
SDA2: U1.D17 (PT62A), U10.41 (1A5)
SDA3: U1.A17 (PT58B), U10.40 (1A6)
SDA4: U1.D18 (PT65B), U10.38 (1A7)
SDA5: U1.A19 (PT71B), U10.37 (1A8)
SDA6: U1.C19 (PT69A), U10.36 (2A1)
SDA7: U1.E19 (PT67A), U10.35 (2A2)
SDA8: U1.D21 (PT78A), U10.33 (2A3)
SDA9: U1.B21 (PT76A), U10.32 (2A4)
SDA10: U1.D22 (PT80B), U10.30 (2A5)
SDA11: U1.A22 (PT74B), U10.29 (2A6)
SDA12: U1.A23 (PT83A), U10.27 (2A7)
SDA13: U1.A25 (PT85B/URC_GPLL1C_IN), U10.26 (2A8)
SDA14: U1.B26 (PR14C), U11.47 (1A1)
SDA15: U1.C23 (PR11C), U11.46 (1A2)
SDD0: U1.C22 (PT80A), U13.47 (1A1)
SDD1: U1.B23 (PT83B), U13.46 (1A2)
SDD2: U1.A24 (PT85A/URC_GPLL1T_IN), U13.44 (1A3)
SDD3: U1.B24 (PR14D), U13.43 (1A4)
SDD4: U1.C24 (PR11D), U13.41 (1A5)
SDD5: U1.C26 (PR11B/URC_GPLL0C_IN), U13.40 (1A6)
SDD6: U1.D26 (PR17D), U13.38 (1A7)
SDD7: U1.D24 (PR14B), U13.37 (1A8)
SDMRD: U1.C25 (PR11A/URC_GPLL0T_IN), U11.44 (1A3)
SDPA8: J5.11, U1.W22 (PR56C)
SDPA9: J5.14, U1.AA1 (PB4A/D7/IO7)
SDPA10: J5.17, U1.AB2 (PB13A/SN/CSN)
SDPA11: J5.19, U1.AC1 (PB6A/D5/MISO2/IO5)
SDPAD0: J4.70, U1.T23 (PR50D)
SDPAD1: J4.73, U1.U25 (PR65B)
SDPAD2: J4.75, U1.U24 (PR59B)
SDPAD3: J4.78, U1.U22 (PR53B)
SDPAD4: J5.1, U1.V24 (PR68A)
SDPAD5: J5.3, U1.V21 (PR56B)
SDPAD6: J5.6, U1.W24 (PR68D/LRC_GPLL0C_IN)
SDPAD7: J5.9, U1.W26 (PR68B)
SDPMPX: J5.22, U1.AD1 (PB6B/D4/MOSI2/IO4)
SDPOE: J5.25, U1.N4 (PL47D)
SDRA8: J5.7, U1.W25 (PR68C/LRC_GPLL0T_IN)
SDRA9: J5.10, U1.W21 (PR56D)
SDRA20: J5.13, U1.W23 (PR56A)
SDRA21: J5.15, U1.AB1 (PB4B/D6/IO6)
SDRA22: J5.18, U1.AB3 (PB15B/DOUT/CSON)
SDRA23: J5.21, U1.AC2 (PB13B/CS1N)
SDRAD0: J4.66, U1.T26 (PR65D)
SDRAD1: J4.69, U1.T24 (PR59A)
SDRAD2: J4.71, U1.T22 (PR50B)
SDRAD3: J4.74, U1.U26 (PR65C)
SDRAD4: J4.77, U1.U23 (PR53D)
SDRAD5: J4.79, U1.U21 (PR53C)
SDRAD6: J5.2, U1.V26 (PR65A)
SDRAD7: J5.5, U1.V23 (PR53A)
SDRD0: U1.A16 (PT58A), U10.47 (1A1)
SDRD1: U1.B16 (PT56A), U10.46 (1A2)
SDRMPX: J5.23, U1.AD3 (PB18A/WRITEN)
SDROE: J5.26, U1.P4 (PL47A)
SDROM: U1.D25 (PR17A), U11.43 (1A4)
SDR_A0: U1.B1 (PL14C), U3.23 (A0), U4.23 (A0)
SDR_A1: U1.B3 (PL14D), U3.24 (A1), U4.24 (A1)
SDR_A2: U1.C2 (PL11A/ULC_GPLL0T_IN), U3.25 (A2), U4.25 (A2)
SDR_A3: U1.C1 (PL11B/ULC_GPLL0C_IN), U3.26 (A3), U4.26 (A3)
SDR_A4: U1.C4 (PL11C), U3.29 (A4), U4.29 (A4)
SDR_A5: U1.C3 (PL11D), U3.30 (A5), U4.30 (A5)
SDR_A6: U1.D4 (PL14A), U3.31 (A6), U4.31 (A6)
SDR_A7: U1.D3 (PL14B), U3.32 (A7), U4.32 (A7)
SDR_A8: U1.D2 (PL17A), U3.33 (A8), U4.33 (A8)
SDR_A9: U1.D1 (PL17D), U3.34 (A9), U4.34 (A9)
SDR_A10: U1.E3 (PL17C), U3.22 (A10), U4.22 (A10)
SDR_A11: U1.E1 (PL17B), U3.35 (A11), U4.35 (A11)
SDR_A12: U1.E4 (PL20C), U3.36 (A12), U4.36 (A12)
SDR_BA0: U1.F2 (PL20A), U3.20 (BA0), U4.20 (BA0)
SDR_BA1: U1.F1 (PL20B), U3.21 (BA1), U4.21 (BA1)
SDR_CAS_N: U1.L1 (PL41D), U3.17 (CAS#), U4.17 (CAS#)
SDR_CKE: R26.1, R29.1, U1.K1 (PL41C), U3.37 (CKE), U4.37 (CKE)
SDR_CLK: U1.L5 (PL26D), U3.38 (CLK), U4.38 (CLK)
SDR_CS0_N: R33.1, U1.L4 (PL32B/PCLKC7_1), U3.19 (CS#)
SDR_CS1_N: R32.1, U1.L3 (PL38D), U4.19 (CS#)
SDR_DQ0: U1.F3 (PL20D), U3.2 (DQ0), U4.2 (DQ0)
SDR_DQ1: U1.F5 (PL23A), U3.4 (DQ1), U4.4 (DQ1)
SDR_DQ2: U1.F4 (PL23B), U3.5 (DQ2), U4.5 (DQ2)
SDR_DQ3: U1.H5 (PL23C/VREF1_7), U3.7 (DQ3), U4.7 (DQ3)
SDR_DQ4: U1.H6 (PL23D), U3.8 (DQ4), U4.8 (DQ4)
SDR_DQ5: U1.H4 (PL26C), U3.10 (DQ5), U4.10 (DQ5)
SDR_DQ6: U1.H3 (PL35A/PCLKT6_1), U3.11 (DQ6), U4.11 (DQ6)
SDR_DQ7: U1.H2 (PL35C/PCLKT6_0), U3.13 (DQ7), U4.13 (DQ7)
SDR_DQ8: U1.H1 (PL35D/PCLKC6_0), U3.42 (DQ8), U4.42 (DQ8)
SDR_DQ9: U1.J6 (PL26A), U3.44 (DQ9), U4.44 (DQ9)
SDR_DQ10: U1.J4 (PL29B), U3.45 (DQ10), U4.45 (DQ10)
SDR_DQ11: U1.J3 (PL35B/PCLKC6_1), U3.47 (DQ11), U4.47 (DQ11)
SDR_DQ12: U1.J1 (PL38B), U3.48 (DQ12), U4.48 (DQ12)
SDR_DQ13: U1.K6 (PL26B), U3.50 (DQ13), U4.50 (DQ13)
SDR_DQ14: U1.K5 (PL29A/GR_PCLK7_1), U3.51 (DQ14), U4.51 (DQ14)
SDR_DQ15: U1.K4 (PL32A/PCLKT7_1), U3.53 (DQ15), U4.53 (DQ15)
SDR_DQM0: R27.1, R30.1, U1.K2 (PL38A/GR_PCLK6_0), U3.15 (LDQM), U4.15 (LDQM)
SDR_DQM1: R28.1, R31.1, U1.K3 (PL38C/GR_PCLK6_1), U3.39 (UDQM), U4.39 (UDQM)
SDR_RAS_N: U1.L2 (PL41A), U3.18 (RAS#), U4.18 (RAS#)
SDR_WE_N: U1.M6 (PL29C/GR_PCLK7_0), U3.16 (WE#), U4.16 (WE#)
SPI_CS_N: J5.31, R23.1, U1.M1 (PL41B)
SPI_IO0: J5.33, U1.M3 (PL44D)
SPI_IO1: J5.34, U1.N6 (PL32C/PCLKT7_0)
SPI_IO2: J5.35, U1.N5 (PL32D/PCLKC7_0)
SPI_IO3: J5.37, U1.N1 (PL44A)
SPI_SCLK: J5.30, U1.M4 (PL29D)
VCCAUX_F: C28.1, C29.1, C30.1, C31.1, C32.1, C33.1, C34.1, C35.1, C36.1, C37.1, FB1.2, U1.H11 (VCCAUX), U1.H14 (VCCAUX), U1.H17 (VCCAUX), U1.K19 (VCCAUX), U1.L8 (VCCAUX), U1.T8 (VCCAUX), U1.T19 (VCCAUX), U1.W8 (VCCAUX), U1.W19 (VCCAUX)
X_2H1: J2.6, U8.6 (1B4)
X_8M: J3.48, U11.9 (1B6)
X_12M: J2.5, U8.5 (1B3)
X_24M: J2.48, U11.8 (1B5)
X_CA4: J2.10, U8.12 (1B8)
X_DOTA: J3.30, U12.2 (1B1)
X_DOTB: J3.31, U12.3 (1B2)
X_EVEN: J2.7, U8.8 (1B5)
X_FIXD0: J3.3, U11.13 (2B1)
X_FIXD1: J3.4, U11.14 (2B2)
X_FIXD2: J3.5, U11.16 (2B3)
X_FIXD3: J3.6, U11.17 (2B4)
X_FIXD4: J3.7, U11.19 (2B5)
X_FIXD5: J3.8, U11.20 (2B6)
X_FIXD6: J3.9, U11.22 (2B7)
X_FIXD7: J3.10, U11.23 (2B8)
X_GAD0: J3.32, U12.5 (1B3)
X_GAD1: J3.33, U12.6 (1B4)
X_GAD2: J3.34, U12.8 (1B5)
X_GAD3: J3.35, U12.9 (1B6)
X_GBD0: J3.36, U12.11 (1B7)
X_GBD1: J3.37, U12.12 (1B8)
X_GBD2: J3.38, U12.13 (2B1)
X_GBD3: J3.39, U12.14 (2B2)
X_H: J2.8, U8.9 (1B6)
X_LOAD: J2.9, U8.11 (1B7)
X_P0: J2.11, U8.13 (2B1)
X_P1: J3.11, U8.14 (2B2)
X_P2: J2.12, U8.16 (2B3)
X_P3: J3.12, U8.17 (2B4)
X_P4: J2.13, U8.19 (2B5)
X_P5: J3.13, U8.20 (2B6)
X_P6: J2.14, U8.22 (2B7)
X_P7: J3.14, U8.23 (2B8)
X_P8: J2.15, U9.2 (1B1)
X_P9: J3.15, U9.3 (1B2)
X_P10: J2.16, U9.5 (1B3)
X_P11: J3.16, U9.6 (1B4)
X_P12: J2.17, U9.8 (1B5)
X_P13: J3.17, U9.9 (1B6)
X_P14: J2.18, U9.11 (1B7)
X_P15: J3.18, U9.12 (1B8)
X_P16: J2.19, U9.13 (2B1)
X_P17: J3.19, U9.14 (2B2)
X_P18: J2.20, U9.16 (2B3)
X_P19: J3.20, U9.17 (2B4)
X_P20: J2.21, U9.19 (2B5)
X_P21: J3.21, U9.20 (2B6)
X_P22: J2.22, U9.22 (2B7)
X_P23: J3.22, U9.23 (2B8)
X_PCK1B: J2.3, U8.2 (1B1)
X_PCK2B: J2.4, U8.3 (1B2)
X_SDA0: J2.30, U10.5 (1B3)
X_SDA1: J2.31, U10.6 (1B4)
X_SDA2: J2.32, U10.8 (1B5)
X_SDA3: J2.33, U10.9 (1B6)
X_SDA4: J2.34, U10.11 (1B7)
X_SDA5: J2.35, U10.12 (1B8)
X_SDA6: J2.36, U10.13 (2B1)
X_SDA7: J2.37, U10.14 (2B2)
X_SDA8: J2.38, U10.16 (2B3)
X_SDA9: J2.39, U10.17 (2B4)
X_SDA10: J2.40, U10.19 (2B5)
X_SDA11: J2.41, U10.20 (2B6)
X_SDA12: J2.42, U10.22 (2B7)
X_SDA13: J2.43, U10.23 (2B8)
X_SDA14: J2.44, U11.2 (1B1)
X_SDA15: J2.45, U11.3 (1B2)
X_SDD0: J3.40, U13.2 (1B1)
X_SDD1: J3.41, U13.3 (1B2)
X_SDD2: J3.42, U13.5 (1B3)
X_SDD3: J3.43, U13.6 (1B4)
X_SDD4: J3.44, U13.8 (1B5)
X_SDD5: J3.45, U13.9 (1B6)
X_SDD6: J3.46, U13.11 (1B7)
X_SDD7: J3.47, U13.12 (1B8)
X_SDMRD: J2.46, U11.5 (1B3)
X_SDRD0: J2.28, U10.2 (1B1)
X_SDRD1: J2.29, U10.3 (1B2)
X_SDROM: J2.47, U11.6 (1B4)

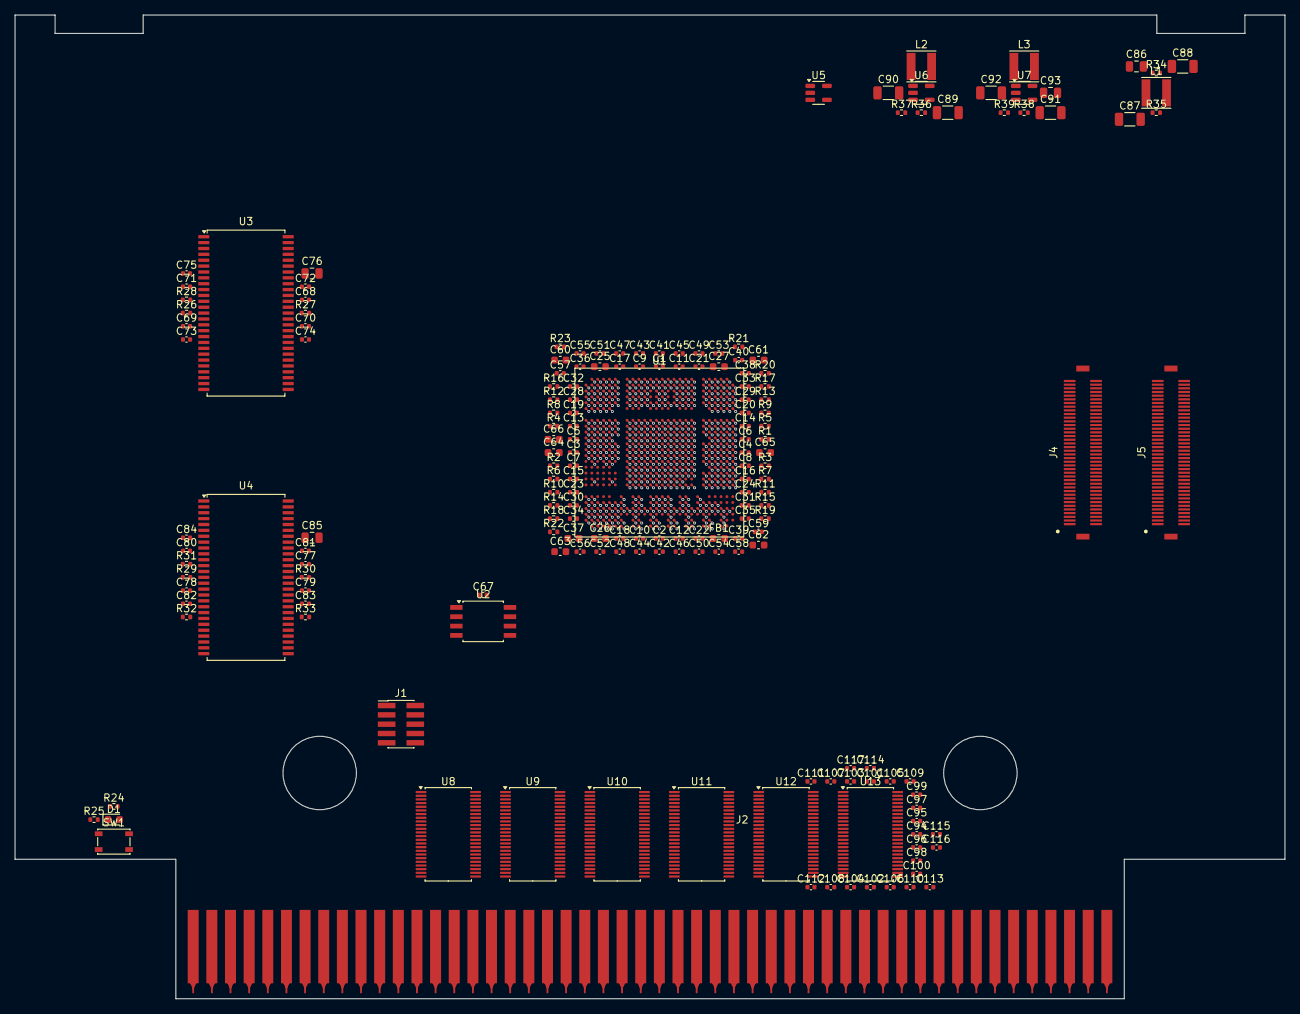
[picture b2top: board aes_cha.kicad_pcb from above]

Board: 6 copper layers, 173.0 x 134.0 mm, 180 parts (1 on the bottom side), 327 nets.

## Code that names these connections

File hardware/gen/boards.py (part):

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    b.r("LED_A", "FPGA_DONE", "1k"); b.r("LED_K", GND, "0")
    b.add("SW", "Switch:SW_Push", "PROGRAMN", "Button_Switch_SMD:SW_SPST_PTS810", {"1": "FPGA_PROGRAMN", "2": GND})
    jt = b.stock("J", "Connector_Generic", "Conn_02x05_Odd_Even", "JTAG", "Connector_PinHeader_1.27mm:PinHeader_2x05_P1.27mm_Vertical_SMD",
                 {"1": V3, "2": "JTAG_TMS", "3": GND, "4": "JTAG_TCK", "5": GND, "6": "JTAG_TDO", "8": "JTAG_TDI", "9": GND},   # ARM Cortex Debug 10-pin 1.27 mm (Tigard, J-Link, ...)
                 default=None)
    # SPI flash
    b.stock("U", "Memory_Flash", "W25Q128JVS", "W25Q128JVS", "Package_SO:SOIC-8W_5.3x5.3mm_P1.27mm",
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          "20": "XIN", "21": "XOUT", "26": "RP_RUN", "24": "SWCLK", "25": "SWD",
          "46": "USB_DM_R", "47": "USB_DP_R",
          "51": "QSPI_SD3", "52": "QSPI_SCLK", "53": "QSPI_SD0", "54": "QSPI_SD2", "55": "QSPI_SD1", "56": "QSPI_SS",
          # SPI/quad link to the FPGA on GPIO0-5, SD on GPIO6-11, control on 12-14, LED 25
          "2": "SPI_SCLK", "3": "SPI_CS_N", "4": "SPI_IO0", "5": "SPI_IO1", "6": "SPI_IO2", "7": "SPI_IO3",
          "8": "SD_CLK", "9": "SD_CMD", "11": "SD_D0", "12": "SD_D1", "13": "SD_D2", "14": "SD_D3",
          "15": "SD_DET", "16": "MCU_RUN", "17": "MCU_INT", "37": "LED_MCU"}
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    b.add("SW", "Switch:SW_Push", "BOOTSEL", "Button_Switch_SMD:SW_SPST_PTS810", {"1": "BOOTSEL_N", "2": GND})
    b.r("BOOTSEL_N", "QSPI_SS", "1k")
    b.r("USB_DM_R", "USB_DM", "27"); b.r("USB_DP_R", "USB_DP", "27")
    b.stock("J", "Connector_Generic", "Conn_01x04", "USB/SWD pads", "Connector_PinHeader_1.27mm:PinHeader_1x04_P1.27mm_Vertical",
            {"1": "USB_DM", "2": "USB_DP", "3": GND, "4": V5})
    b.stock("J", "Connector_Generic", "Conn_01x03", "SWD", "Connector_PinHeader_1.27mm:PinHeader_1x03_P1.27mm_Vertical",
            {"1": "SWCLK", "2": GND, "3": "SWD"})
    # 12 MHz crystal
    b.add("Y", "Device:Crystal_GND24", "12MHz ABM8-272-T3", "Crystal:Crystal_SMD_3225-4Pin_3.2x2.5mm",
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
